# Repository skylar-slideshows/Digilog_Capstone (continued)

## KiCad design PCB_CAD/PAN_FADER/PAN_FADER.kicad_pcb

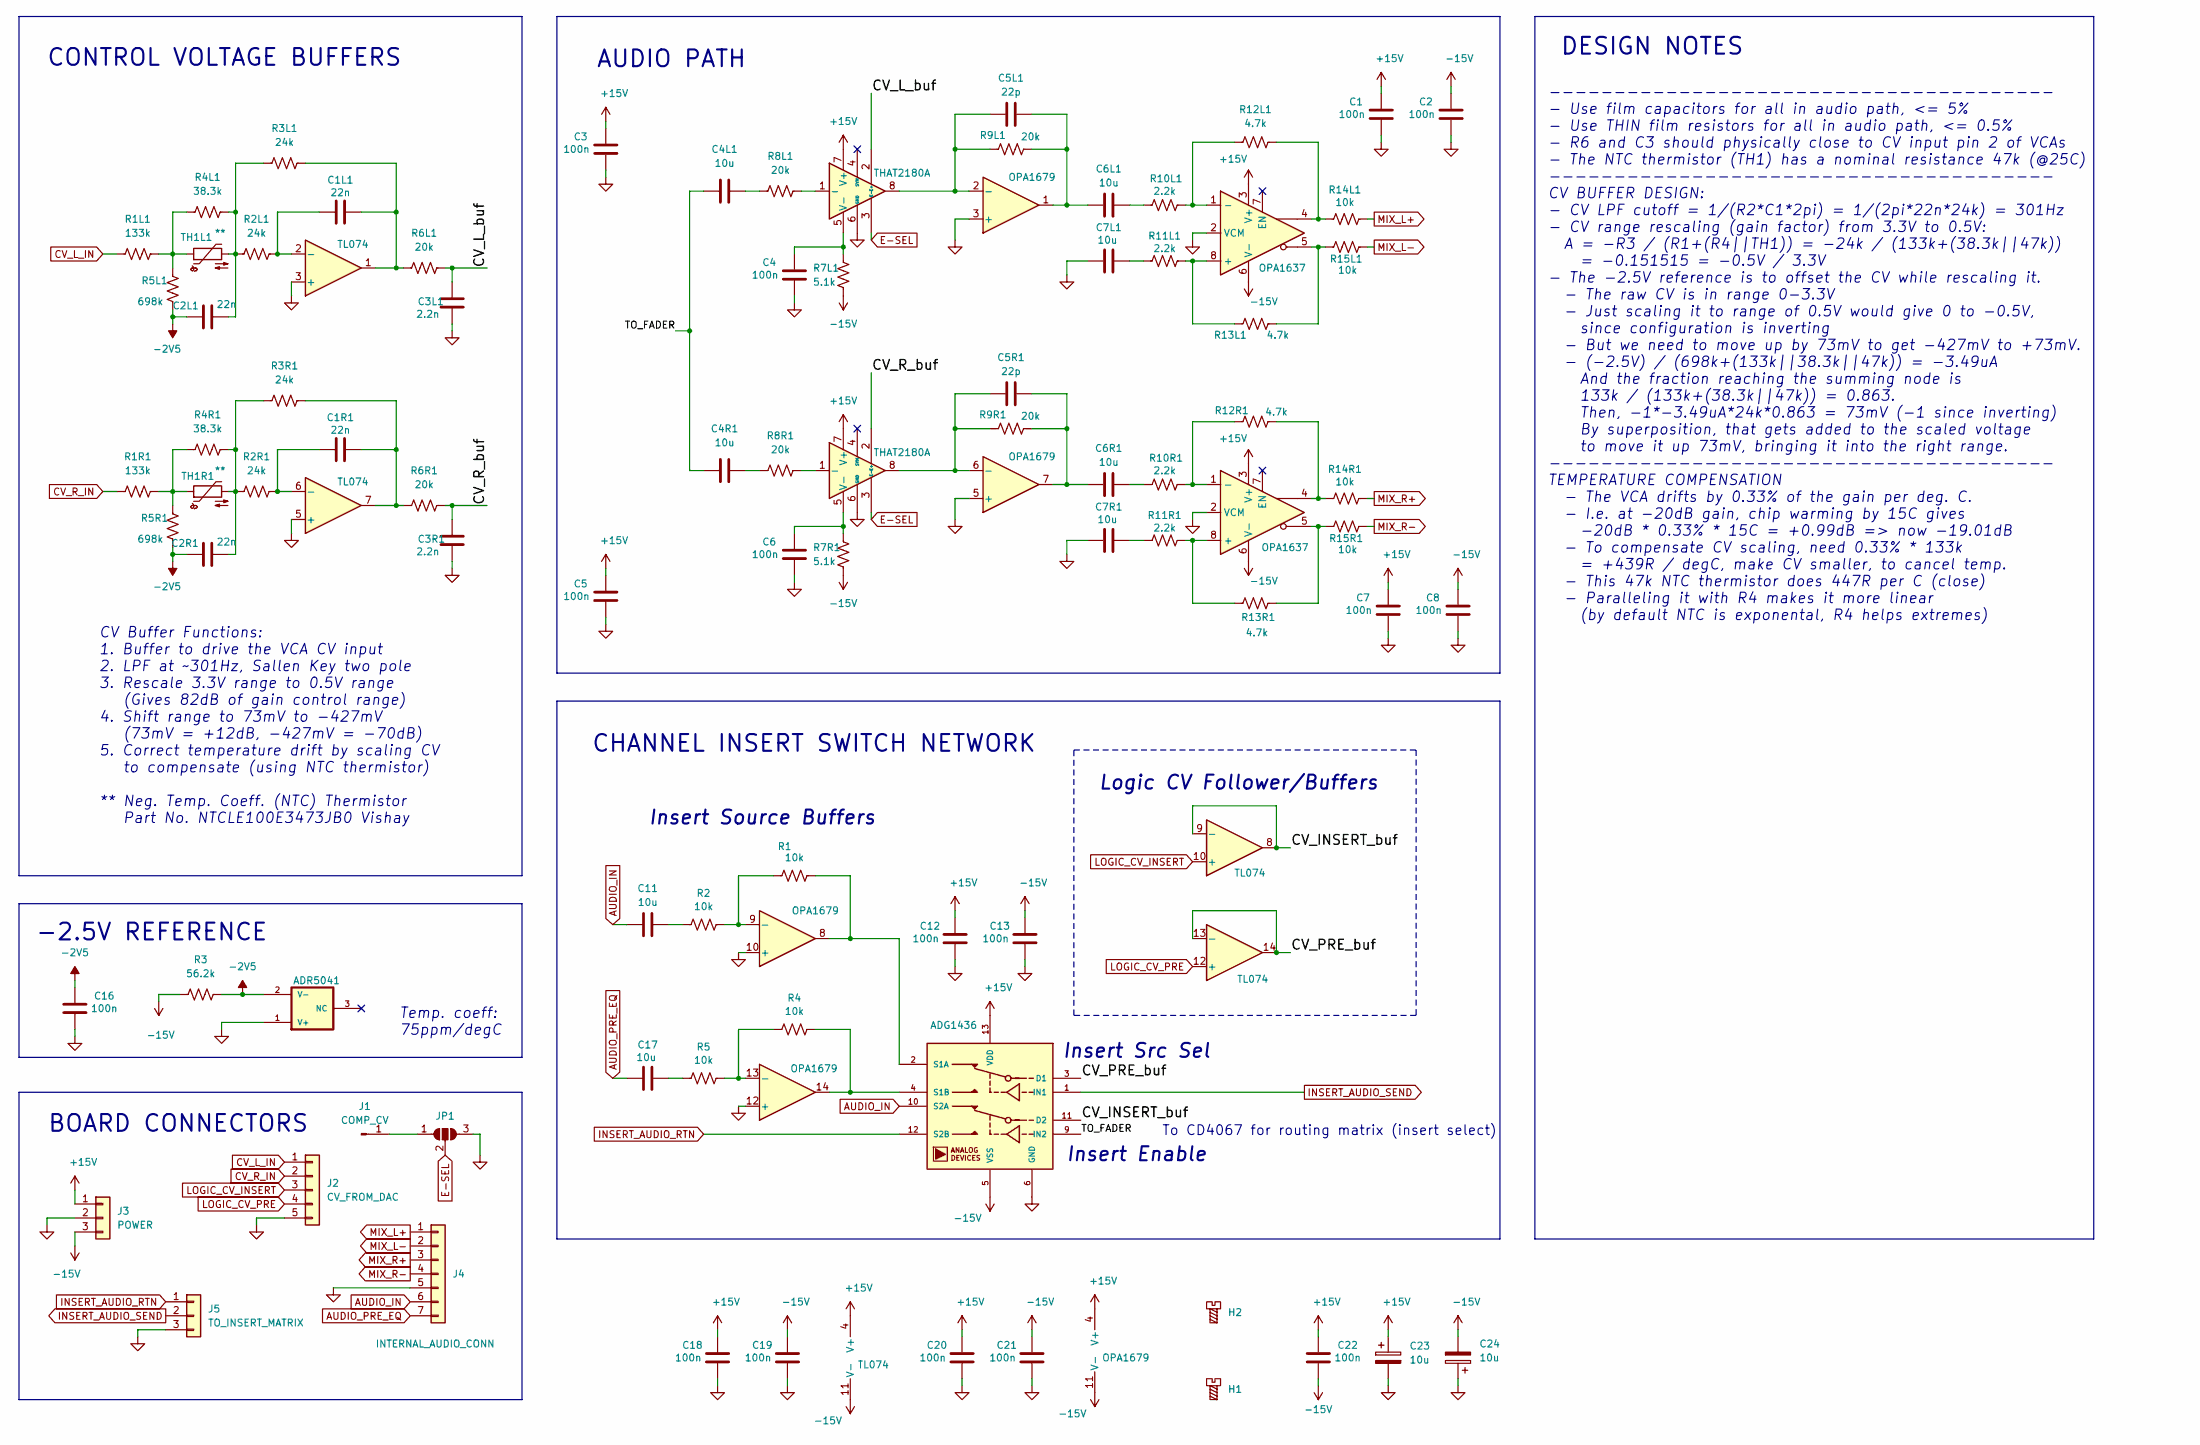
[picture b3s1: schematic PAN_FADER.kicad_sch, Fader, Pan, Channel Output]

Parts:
C1, C2, C3, C4, C5, C6, C7, C8, C12, C13, C16, C18, C19, C20, C21, C22: 100n; C_0603_1608Metric; LCSC C1591
C1L1, C1R1, C2L1, C2R1: 22n; C_Rect_L7.2mm_W2.5mm_P5.00mm; LCSC DNP
C3L1, C3R1: 2.2n; C_Rect_L7.2mm_W2.5mm_P5.00mm; LCSC DNP
C4L1, C4R1, C6L1, C6R1, C7L1, C7R1, C11, C17: 10u; CP_Elec_6.3x5.4_Nichicon; LCSC C340735
C5L1, C5R1: 22p; C_0603_1608Metric; LCSC C105620
C23, C24: 10u; C_1206_3216Metric; LCSC C9807
H1, H2: MountingHole_Pad; MountingHole_2.2mm_M2
J1: COMP_CV; PinHeader_1x01_P2.54mm_Vertical; LCSC DNP
J2: CV_FROM_DAC; PinHeader_1x05_P2.54mm_Vertical; Part Number 1-0301FBV0T; LCSC DNP
J3: POWER; PinHeader_1x03_P2.54mm_Vertical; Part Number 1-0301FBV0T; LCSC DNP
J4: INTERNAL_AUDIO_CONN; PinHeader_1x07_P2.54mm_Vertical; Part Number 1-0301FBV0T; LCSC DNP
J5: TO_INSERT_MATRIX; PinHeader_1x03_P2.54mm_Vertical; Part Number 1-0301FBV0T; LCSC DNP
JP1: SolderJumper_3_Open; SolderJumper-3_P2.0mm_Open_TrianglePad1.0x1.5mm; LCSC DNP
R1, R2, R4, R5, R14L1, R14R1, R15L1, R15R1: 10k; R_0603_1608Metric; LCSC C95204
R1L1, R1R1: 133k; R_0402_1005Metric; LCSC C852517
R2L1, R2R1, R3L1, R3R1: 24k; R_0603_1608Metric; LCSC C319717
R3: 56.2k; R_0402_1005Metric; LCSC C705626
R4L1, R4R1: 38.3k; R_0603_1608Metric; LCSC C861362
R5L1, R5R1: 698k; R_0805_2012Metric; LCSC C865618
R6L1, R6R1, R8L1, R8R1, R9L1, R9R1: 20k; R_0603_1608Metric; LCSC C154077
R7L1, R7R1: 5.1k; R_0603_1608Metric; LCSC C122969
R10L1, R10R1, R11L1, R11R1: 2.2k; R_0402_1005Metric; LCSC C326602
R12L1, R12R1, R13L1, R13R1: 4.7k; R_0402_1005Metric; LCSC C281778
TH1L1, TH1R1: **; R_Axial_DIN0207_L6.3mm_D2.5mm_P2.54mm_Vertical; LCSC DNP
U1, U5: THAT2180A; SIP-8_19x3mm_P2.54mm; LCSC DNP
U2: OPA1679; SOIC-14_3.9x8.65mm_Pitch1.27mm; LCSC C2878631
U3, U7: OPA1637; Texas_S-PDSO-G8_3x3mm_P0.65mm; LCSC C2860968
U4: TL074; SOIC-14_3.9x8.7mm_P1.27mm; LCSC C12594
U8: ADR5041; SOT-23-3; MPN ADR5041ARTZ-R2; LCSC C659596
U9: ADG1436; TSSOP-16_4.4x5mm_P0.65mm; LCSC C408899

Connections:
+15V: C1.2, C3.2, C5.2, C7.2, C12.2, C18.2, C20.2, C22.2, C23.1, J3.1, U1.7 (V+), U2.4 (V+), U3.3 (V+), U4.4 (V+), U5.7 (V+), U7.3 (V+), U9.13 (VDD)
-2V5: C2L1.1, C2R1.1, C16.2, R3.2, R5L1.1, R5R1.1, U8.2 (V-)
-15V: C2.2, C8.2, C13.2, C19.2, C21.2, C22.1, C24.2, J3.3, R3.1, R7L1.1, R7R1.1, U2.11 (V-), U3.6 (V-), U4.11 (V-), U7.6 (V-), U9.5 (VSS)
/CV_INSERT_buf: U4.8, U4.9 (-), U9.11 (D2)
/CV_L_buf: C3L1.2, R6L1.2, U1.2 (E+)
/CV_PRE_buf: U4.13 (-), U4.14, U9.3 (D1)
/CV_R_buf: C3R1.2, R6R1.2, U5.2 (E+)
/TO_FADER: C4L1.1, C4R1.1, U9.9 (IN2)
AUDIO_IN: C11.1, J4.6, U9.10 (S2A)
AUDIO_PRE_EQ: C17.1, J4.7
CV_L_IN: J2.1, R1L1.1
CV_R_IN: J2.2, R1R1.1
E-SEL: JP1.2 (C), U1.3 (E-), U5.3 (E-)
GND: C1.1, C2.1, C3.1, C3L1.1, C3R1.1, C4.1, C5.1, C6.1, C7.1, C7L1.1, C7R1.1, C8.1, C12.1, C13.1, C16.1, C18.1, C19.1, C20.1, C21.1, C23.2, C24.1, J2.5, J3.2, J4.5, J5.3, JP1.3 (B), U1.6 (GND), U2.3 (+), U2.5 (+), U2.10 (+), U2.12 (+), U3.2 (VCM), U4.3 (+), U4.5 (+), U5.6 (GND), U7.2 (VCM), U8.1 (V+), U9.6 (GND)
INSERT_AUDIO_RTN: J5.1, U9.12 (S2B)
INSERT_AUDIO_SEND: J5.2, U9.1 (IN1)
LOGIC_CV_INSERT: J2.3, U4.10 (+)
LOGIC_CV_PRE: J2.4, U4.12 (+)
MIX_L+: J4.1, R14L1.2
MIX_L-: J4.2, R15L1.2
MIX_R+: J4.3, R14R1.2
MIX_R-: J4.4, R15R1.2
unnamed: C1L1.2, R3L1.2, R6L1.1, U4.1
unnamed: C1R1.2, R3R1.2, R6R1.1, U4.7
unnamed: C2L1.2, R2L1.1, R3L1.1, R4L1.2, TH1L1.2
unnamed: C2R1.2, R2R1.1, R3R1.1, R4R1.2, TH1R1.2
unnamed: C4L1.2, R8L1.1
unnamed: C4R1.2, R8R1.1
unnamed: C5L1.2, C6L1.1, R9L1.2, U2.1
unnamed: C5R1.2, C6R1.1, R9R1.2, U2.7
unnamed: C6L1.2, R10L1.1
unnamed: C6R1.2, R10R1.1
unnamed: C7L1.2, R11L1.1
unnamed: C7R1.2, R11R1.1
unnamed: C11.2, R2.2
unnamed: C17.2, R5.2
unnamed: J1.1 (Pin_1_1), JP1.1 (A)
unnamed: R1L1.2, R4L1.1, R5L1.2, TH1L1.1
unnamed: R1R1.2, R4R1.1, R5R1.2, TH1R1.1
unnamed: R12L1.2, R14L1.1, U3.4
unnamed: R12R1.2, R14R1.1, U7.4
unnamed: R13L1.2, R15L1.1, U3.5
unnamed: R13R1.2, R15R1.1, U7.5
unnamed: R8L1.2, U1.1 (-)
unnamed: C4.2, R7L1.2, U1.5 (V-)
unnamed: C5L1.1, R9L1.1, U1.8, U2.2 (-)
unnamed: C5R1.1, R9R1.1, U2.6 (-), U5.8
unnamed: R1.2, R2.1, U2.9 (-)
unnamed: R4.2, R5.1, U2.13 (-)
unnamed: R11L1.2, R13L1.1, U3.8 (+)
unnamed: R10L1.2, R12L1.1, U3.1 (-)
unnamed: C1L1.1, R2L1.2, U4.2 (-)
unnamed: C1R1.1, R2R1.2, U4.6 (-)
unnamed: R8R1.2, U5.1 (-)
unnamed: C6.2, R7R1.2, U5.5 (V-)
unnamed: R11R1.2, R13R1.1, U7.8 (+)
unnamed: R10R1.2, R12R1.1, U7.1 (-)
unnamed: R1.1, U2.8, U9.2 (S1A)
unnamed: R4.1, U2.14, U9.4 (S1B)

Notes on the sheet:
CONTROL VOLTAGE BUFFERS
--------------------------------------- - Use film capacitors for all in audio path, <= 5% - Use THIN film resistors for all in audio path, <= 0.5% - R6 and C3 should physically close to CV input pin 2 of VCAs - The NTC thermistor (TH1) has a nominal resistance 47k (@25C) --------------------------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
BOARD CONNECTORS
Logic CV Follower/Buffers
CV Buffer Functions: 1. Buffer to drive the VCA CV input 2. LPF at ~301Hz, Sallen Key two pole 3. Rescale 3.3V range to 0.5V range (Gives 82dB of gain control range) 4. Shift range to 73mV to -427mV (73mV = +12dB, -427mV = -70dB) 5. Correct temperature drift by scaling CV to compensate (using NTC t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
Insert Source Buffers
Insert Enable
AUDIO PATH
Insert Src Sel
-2.5V REFERENCE
CHANNEL INSERT SWITCH NETWORK
Temp. coeff: 75ppm/degC
DESIGN NOTES
To CD4067 for routing matrix (insert select)

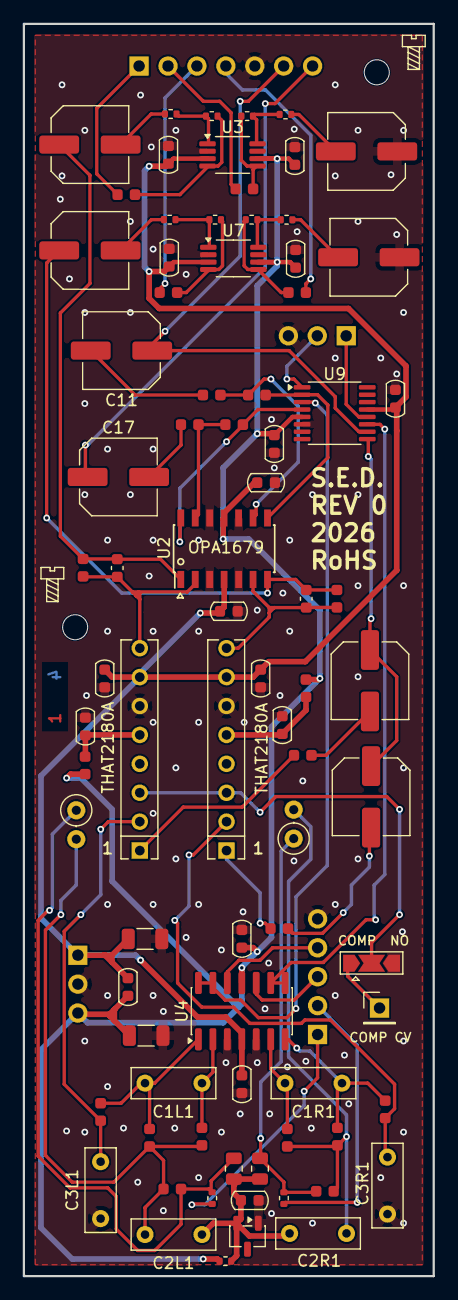
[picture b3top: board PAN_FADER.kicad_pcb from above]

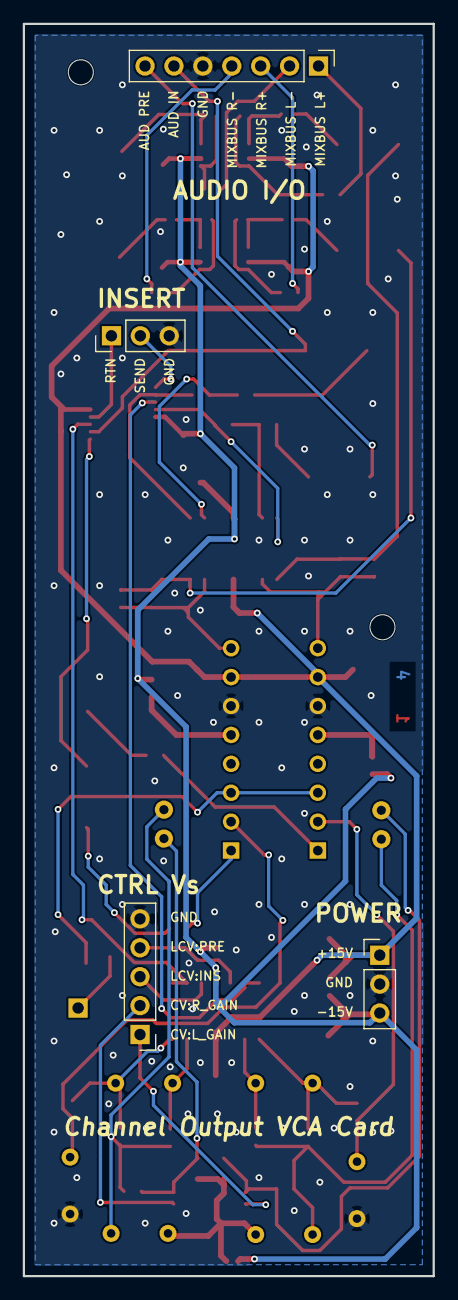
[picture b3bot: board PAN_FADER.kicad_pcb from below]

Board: 4 copper layers, 36.0 x 110.0 mm, 87 parts (4 on the bottom side), 59 nets.

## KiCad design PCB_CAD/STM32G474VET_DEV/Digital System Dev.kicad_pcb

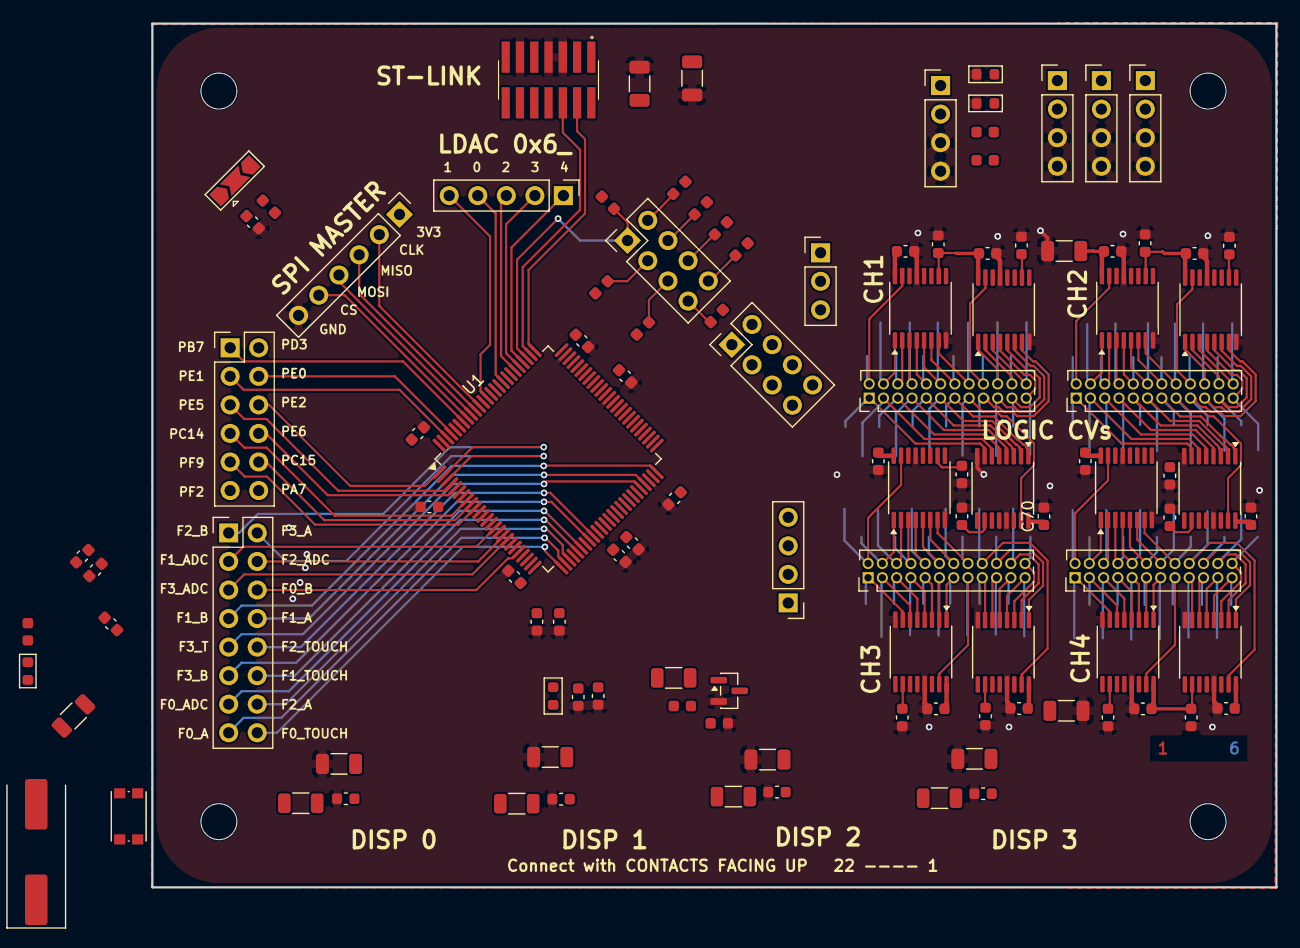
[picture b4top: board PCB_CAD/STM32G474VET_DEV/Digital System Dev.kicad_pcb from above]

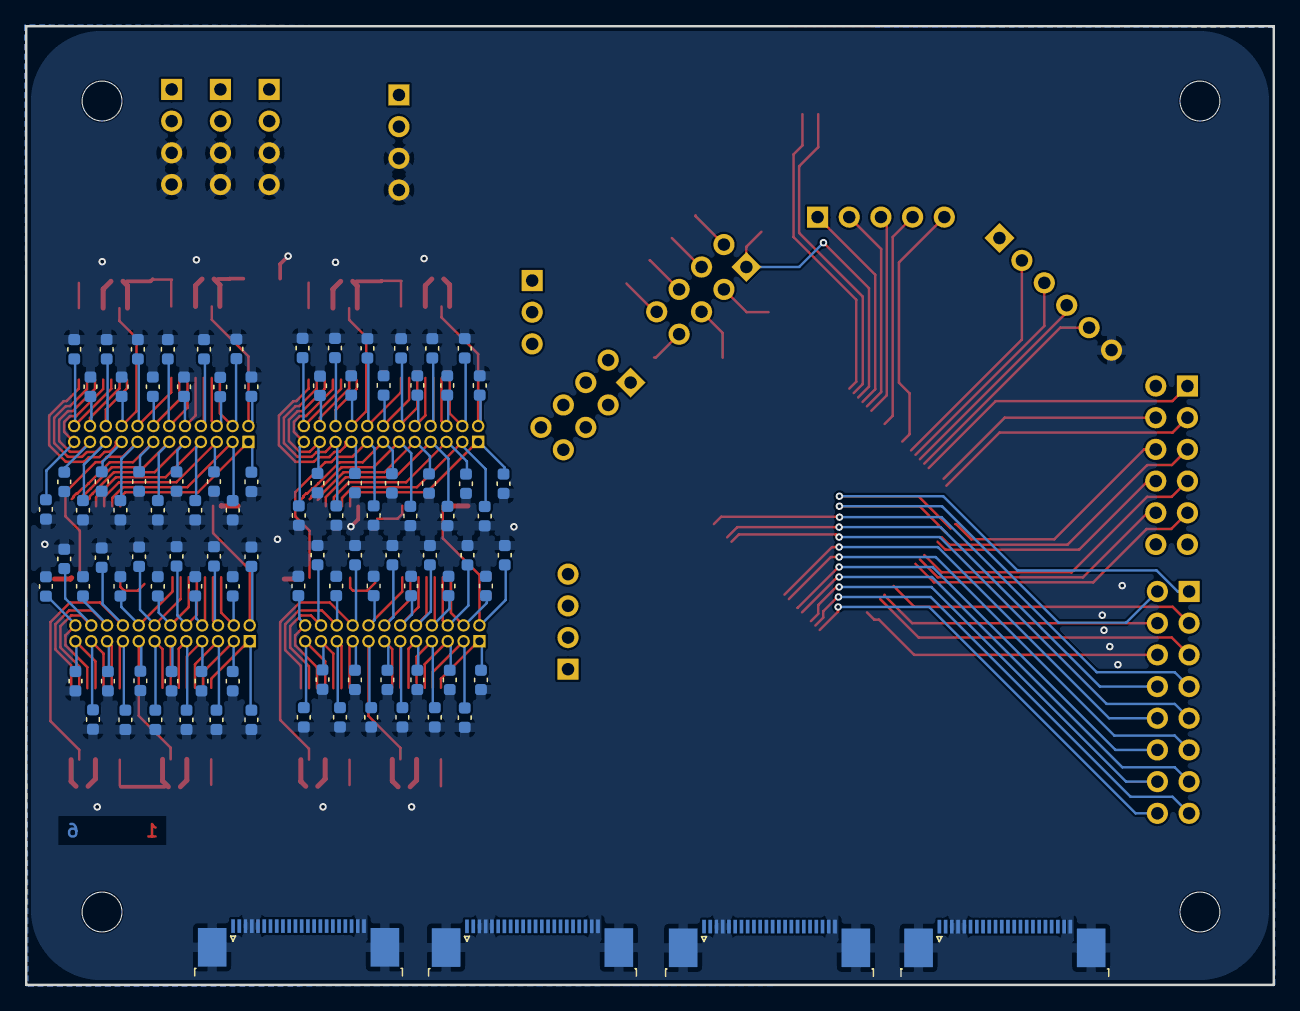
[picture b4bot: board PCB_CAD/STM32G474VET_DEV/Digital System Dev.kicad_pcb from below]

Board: 6 copper layers, 100.0 x 76.8 mm, 214 parts (100 on the bottom side), 209 nets.

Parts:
C1, C2: 20p; C_0603_1608Metric
C3, C5, C7, C8, C9, C10, C11, C12, C13, C14, C15, C16, C35, C36, C37, C38, C62, C63, C64, C65, C66, C67, C68, C69, C70, C71, C72, C73, C74, C75, C76, C77, C78, C79, C80, C81, C82, C83, C84, C85, C86, C87, C88, C89, C90, C91, C92, C93, C94, C95, C96, C97, C98, C99, C100, C101, C102, C103, C104, C105, C106, C107, C108, C109, C110, C111, C112, C113, C114, C115, C116, C117, C118, C119, C120, C121, C122, C123, C124, C125, C126, C127, C128, C129, C130, C131, C132, C133, C134, C135, C136, C137, C138, C139, C140, C141, C142, C143, C144, C145, C146, C147, C148, C149, C150, C151, C152, C153, C154, C155, C156, C157, C158, C159, C160, C161, C162, C163, C164, C165, C166, C167, C168, C169, C170, C171, C172, C173, C174, C175, C176, C177, C178, C179, C180, C181: 100n; C_0603_1608Metric
C4, C6: 1u; C_0603_1608Metric
C41, C42, C47, C48, C49, C50, C60, C61: 10u; C_1206_3216Metric
D3, D6, D7: LED; LED_0603_1608Metric
FB1: FerriteBead; Ferrite_0603_1608Metric
H1, H2, H3, H4: MountingScrew; MountingHole_3.2mm_M3
J1: STLINK; FTSH-107-01-L-DV-K-TR
J7: SPI_MASTER; PinHeader_1x06_P2.54mm_Vertical
J9, J12, J13, J14: EXT_POW_IN; PinHeader_1x04_P2.54mm_Vertical
J15: LDAC; PinHeader_1x05_P2.54mm_Vertical
J16: FADER; PinHeader_2x08_P2.54mm_Vertical
J17: DISP0; TE_2-1734839-2_1x22-1MP_P0.5mm_Horizontal
J18: DISP1; TE_2-1734839-2_1x22-1MP_P0.5mm_Horizontal
J19: DISP2; TE_2-1734839-2_1x22-1MP_P0.5mm_Horizontal
J20: DISP3; TE_2-1734839-2_1x22-1MP_P0.5mm_Horizontal
J21: EXTRA; PinHeader_2x06_P2.54mm_Vertical
J22: COMP; PinHeader_2x04_P2.54mm_Vertical
J23: LEDs; PinHeader_1x04_P2.54mm_Vertical
J24: I2C; PinHeader_2x04_P2.54mm_Vertical
J25: SHIFTREG; PinHeader_1x03_P2.54mm_Vertical
J26: CV_SW_1; PinHeader_2x12_P1.27mm_Vertical
J27: CV_SW_2; PinHeader_2x12_P1.27mm_Vertical
J28: CV_SW_4; PinHeader_2x12_P1.27mm_Vertical
J29: CV_SW_3; PinHeader_2x12_P1.27mm_Vertical
Q1: 2N7002; SOT-23
R1, R18, R19, R20, R21: 390; R_1206_3216Metric
R2: 10k; R_0603_1608Metric
R7, R8, R9, R10, R11, R12, R13, R14: 1.5k; R_0603_1608Metric
R23, R24: 680; R_0603_1608Metric
R25: 68; R_1206_3216Metric
R26, R27: 47k; R_0603_1608Metric
R28: 3.3k; R_0603_1608Metric
SP1: BOOT_MODE; SolderJumper-3_P2.0mm_Open_TrianglePad1.0x1.5mm
SW1: RESET; SW_Push_1P1T_NO_CK_KMR2
U1: STM32G474VETx; LQFP-100_14x14mm_P0.5mm
U28, U29, U30, U31, U32, U33, U34, U35, U36, U37, U38, U39: 74HC595; TSSOP-16_4.4x5mm_P0.65mm
X1: HSE_24; Crystal_SMD_HC49-SD

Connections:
+3.3VA: C4.1, C5.1, C6.1, C7.1, FB1.2, U1.36 (VREF+), U1.37 (VDDA)
+3V3: C8.1, C9.1, C10.1, C11.1, C12.1, C13.1, C14.1, C15.1, C35.1, C36.1, C37.1, C38.1, C41.1, C42.1, C47.1, C48.1, C49.1, C50.1, C60.1, C61.1, C62.1, C63.1, C64.1, C65.1, C66.1, C67.1, C68.1, C69.1, C70.1, C71.1, C72.1, C73.1, C170.1, C171.1, C172.1, C173.1, C174.1, C175.1, C176.1, C177.1, C178.1, C179.1, C180.1, C181.1, FB1.1, J1.3 (VCC), J7.1, J9.1, J12.1, J13.1, J14.1, J17.6, J18.6, J19.6, J20.6, R7.1, R8.1, R9.1, R10.1, R11.1, R12.1, R13.1, R14.1, R24.1, SP1.3 (B), U1.6 (VBAT), U1.24 (VDD), U1.49 (VDD), U1.64 (VDD), U1.75 (VDD), U1.100 (VDD), U28.10 (~SRCLR), U28.16 (VCC), U29.10 (~SRCLR), U29.16 (VCC), U30.10 (~SRCLR), U30.16 (VCC), U31.10 (~SRCLR), U31.16 (VCC), U32.10 (~SRCLR), U32.16 (VCC), U33.10 (~SRCLR), U33.16 (VCC), U34.10 (~SRCLR), U34.16 (VCC), U35.10 (~SRCLR), U35.16 (VCC), U36.10 (~SRCLR), U36.16 (VCC), U37.10 (~SRCLR), U37.16 (VCC), U38.10 (~SRCLR), U38.16 (VCC), U39.10 (~SRCLR), U39.16 (VCC)
+5V: J9.2, J12.2, J13.2, J14.2, R18.2, R19.2, R20.2, R21.2, R28.1
/cv_sw/1_1: C121.1, J26.23, U32.4 (QE)
/cv_sw/1_2: C122.1, J26.2, U28.15 (QA)
/cv_sw/1_3: C120.1, J26.21, U32.5 (QF)
/cv_sw/1_4: C123.1, J26.4, U28.1 (QB)
/cv_sw/1_5: C119.1, J26.19, U32.6 (QG)
/cv_sw/1_6: C124.1, J26.6, U28.2 (QC)
/cv_sw/1_7: C118.1, J26.17, U32.7 (QH)
/cv_sw/1_8: C125.1, J26.8, U28.3 (QD)
/cv_sw/1_9: C117.1, J26.15, U36.15 (QA)
/cv_sw/1_10: C126.1, J26.10, U28.4 (QE)
/cv_sw/1_11: C116.1, J26.13, U36.1 (QB)
/cv_sw/1_12: C127.1, J26.12, U28.5 (QF)
/cv_sw/1_13: C133.1, J26.11, U36.2 (QC)
/cv_sw/1_14: C110.1, J26.14, U28.6 (QG)
/cv_sw/1_15: C132.1, J26.9, U36.3 (QD)
/cv_sw/1_16: C111.1, J26.16, U28.7 (QH)
/cv_sw/1_17: C131.1, J26.7, U36.4 (QE)
/cv_sw/1_18: C112.1, J26.18, U32.15 (QA)
/cv_sw/1_19: C130.1, J26.5, U36.5 (QF)
/cv_sw/1_20: C113.1, J26.20, U32.1 (QB)
/cv_sw/1_21: C129.1, J26.3, U36.6 (QG)
/cv_sw/1_22: C114.1, J26.22, U32.2 (QC)
/cv_sw/1_23: C128.1, J26.1, U36.7 (QH)
/cv_sw/1_24: C115.1, J26.24, U32.3 (QD)
/cv_sw/2_1: C97.1, J27.23, U33.4 (QE)
/cv_sw/2_2: C146.1, J27.2, U29.15 (QA)
/cv_sw/2_3: C96.1, J27.21, U33.5 (QF)
/cv_sw/2_4: C147.1, J27.4, U29.1 (QB)
/cv_sw/2_5: C95.1, J27.19, U33.6 (QG)
/cv_sw/2_6: C148.1, J27.6, U29.2 (QC)
/cv_sw/2_7: C94.1, J27.17, U33.7 (QH)
/cv_sw/2_8: C149.1, J27.8, U29.3 (QD)
/cv_sw/2_9: C93.1, J27.15, U37.15 (QA)
/cv_sw/2_10: C150.1, J27.10, U29.4 (QE)
/cv_sw/2_11: C92.1, J27.13, U37.1 (QB)
/cv_sw/2_12: C151.1, J27.12, U29.5 (QF)
/cv_sw/2_13: C157.1, J27.11, U37.2 (QC)
/cv_sw/2_14: C86.1, J27.14, U29.6 (QG)
/cv_sw/2_15: C156.1, J27.9, U37.3 (QD)
/cv_sw/2_16: C87.1, J27.16, U29.7 (QH)
/cv_sw/2_17: C155.1, J27.7, U37.4 (QE)
/cv_sw/2_18: C88.1, J27.18, U33.15 (QA)
/cv_sw/2_19: C154.1, J27.5, U37.5 (QF)
/cv_sw/2_20: C89.1, J27.20, U33.1 (QB)
/cv_sw/2_21: C153.1, J27.3, U37.6 (QG)
/cv_sw/2_22: C90.1, J27.22, U33.2 (QC)
/cv_sw/2_23: C152.1, J27.1, U37.7 (QH)
/cv_sw/2_24: C91.1, J27.24, U33.3 (QD)
/cv_sw/3_1: C109.1, J29.23, U34.4 (QE)
/cv_sw/3_2: C134.1, J29.2, U30.15 (QA)
/cv_sw/3_3: C108.1, J29.21, U34.5 (QF)
/cv_sw/3_4: C135.1, J29.4, U30.1 (QB)
/cv_sw/3_5: C107.1, J29.19, U34.6 (QG)
/cv_sw/3_6: C136.1, J29.6, U30.2 (QC)
/cv_sw/3_7: C106.1, J29.17, U34.7 (QH)
/cv_sw/3_8: C137.1, J29.8, U30.3 (QD)
/cv_sw/3_9: C105.1, J29.15, U38.15 (QA)
/cv_sw/3_10: C138.1, J29.10, U30.4 (QE)
/cv_sw/3_11: C104.1, J29.13, U38.1 (QB)
/cv_sw/3_12: C139.1, J29.12, U30.5 (QF)
/cv_sw/3_13: C145.1, J29.11, U38.2 (QC)
/cv_sw/3_14: C98.1, J29.14, U30.6 (QG)
/cv_sw/3_15: C144.1, J29.9, U38.3 (QD)
/cv_sw/3_16: C99.1, J29.16, U30.7 (QH)
/cv_sw/3_17: C143.1, J29.7, U38.4 (QE)
/cv_sw/3_18: C100.1, J29.18, U34.15 (QA)
/cv_sw/3_19: C142.1, J29.5, U38.5 (QF)
/cv_sw/3_20: C101.1, J29.20, U34.1 (QB)
/cv_sw/3_21: C141.1, J29.3, U38.6 (QG)
/cv_sw/3_22: C102.1, J29.22, U34.2 (QC)
/cv_sw/3_23: C140.1, J29.1, U38.7 (QH)
/cv_sw/3_24: C103.1, J29.24, U34.3 (QD)
/cv_sw/4_1: C79.1, J28.23, U35.4 (QE)
/cv_sw/4_2: C164.1, J28.2, U31.15 (QA)
/cv_sw/4_3: C78.1, J28.21, U35.5 (QF)
/cv_sw/4_4: C165.1, J28.4, U31.1 (QB)
/cv_sw/4_5: C77.1, J28.19, U35.6 (QG)
/cv_sw/4_6: C166.1, J28.6, U31.2 (QC)
/cv_sw/4_7: C76.1, J28.17, U35.7 (QH)
/cv_sw/4_8: C167.1, J28.8, U31.3 (QD)
/cv_sw/4_9: C75.1, J28.15, U39.15 (QA)
/cv_sw/4_10: C168.1, J28.10, U31.4 (QE)
/cv_sw/4_11: C74.1, J28.13, U39.1 (QB)
/cv_sw/4_12: C169.1, J28.12, U31.5 (QF)
/cv_sw/4_13: C163.1, J28.11, U39.2 (QC)
/cv_sw/4_14: C85.1, J28.14, U31.6 (QG)
/cv_sw/4_15: C162.1, J28.9, U39.3 (QD)
/cv_sw/4_16: C84.1, J28.16, U31.7 (QH)
/cv_sw/4_17: C161.1, J28.7, U39.4 (QE)
/cv_sw/4_18: C83.1, J28.18, U35.15 (QA)
/cv_sw/4_19: C160.1, J28.5, U39.5 (QF)
/cv_sw/4_20: C82.1, J28.20, U35.1 (QB)
/cv_sw/4_21: C159.1, J28.3, U39.6 (QG)
/cv_sw/4_22: C81.1, J28.22, U35.2 (QC)
/cv_sw/4_23: C158.1, J28.1, U39.7 (QH)
/cv_sw/4_24: C80.1, J28.24, U35.3 (QD)
COMP_ADC0: J22.7, U1.51 (PB12)
COMP_ADC1: J22.4, U1.57 (PD10)
COMP_ADC2: J22.1, U1.60 (PD13)
COMP_ADC3: J22.6, U1.55 (PD8)
COMP_CV0: J22.5, U1.56 (PD9)
COMP_CV1: J22.8, U1.32 (PB0)
COMP_CV2: J22.3, U1.58 (PD11)
COMP_CV3: J22.2, U1.59 (PD12)
DAC_LDAC0: J15.4, U1.84 (PD2)
DAC_LDAC1: J15.5, U1.88 (PD6)
DAC_LDAC2: J15.3, U1.81 (PC12)
DAC_LDAC3: J15.2, U1.80 (PC11)
DAC_LDAC4: J15.1, U1.79 (PC10)
DISP_A0_FMC: J17.17, J18.17, J19.17, J20.17, U1.11 (PF10)
DISP_BL-: J17.2, J18.2, J19.2, J20.2, Q1.3 (D)
DISP_CS0: J17.18, U1.45 (PE14)
DISP_CS1: J18.18, U1.44 (PE13)
DISP_CS2: J19.18, U1.43 (PE12)
DISP_CS3: J20.18, U1.42 (PE11)
DISP_D0_FMC: J17.14, J18.14, J19.14, J20.14, U1.61 (PD14)
DISP_D1_FMC: J17.13, J18.13, J19.13, J20.13, U1.62 (PD15)
DISP_D2_FMC: J17.12, J18.12, J19.12, J20.12, U1.82 (PD0)
DISP_D3_FMC: J17.11, J18.11, J19.11, J20.11, U1.83 (PD1)
DISP_D4_FMC: J17.10, J18.10, J19.10, J20.10, U1.38 (PE7)
DISP_D5_FMC: J17.9, J18.9, J19.9, J20.9, U1.39 (PE8)
DISP_D6_FMC: J17.8, J18.8, J19.8, J20.8, U1.40 (PE9)
DISP_D7_FMC: J17.7, J18.7, J19.7, J20.7, U1.41 (PE10)
DISP_NOE_FMC: J17.15, J18.15, J19.15, J20.15, U1.86 (PD4)
DISP_NWE_FMC: J17.16, J18.16, J19.16, J20.16, U1.87 (PD5)
DISP_PWM: R25.1, U1.71 (PA10)
DISP_RST: J17.20, J18.20, J19.20, J20.20, U1.7 (PC13)
F0_ADC: J16.13, U1.30 (PC4)
F0_MoA: J16.15, U1.27 (PA5)
F0_MoB: J16.6, U1.21 (PA1)
F0_Touch: J16.16, U1.26 (PA4)
F1_ADC: J16.3, U1.15 (PC0)
F1_MoA: J16.8, U1.47 (PB10)
F1_MoB: J16.7, U1.50 (PB11)
F1_Touch: J16.12, U1.31 (PC5)
F2_ADC: J16.4, U1.17 (PC2)
F2_MoA: J16.14, U1.28 (PA6)
F2_MoB: J16.1, U1.2 (PE3)
F2_Touch: J16.10, U1.34 (PB2)
F3_ADC: J16.5, U1.18 (PC3)
F3_MoA: J16.2, U1.3 (PE4)
F3_MoB: J16.11, U1.33 (PB1)
F3_Touch: J16.9, U1.46 (PE15)
GND: C1.2, C2.1, C3.1, C4.2, C5.2, C6.2, C7.2, C8.2, C9.2, C10.2, C11.2, C12.2, C13.2, C14.2, C15.2, C16.2, C35.2, C36.2, C37.2, C38.2, C41.2, C42.2, C47.2, C48.2, C49.2, C50.2, C60.2, C61.2, C62.2, C63.2, C64.2, C65.2, C66.2, C67.2, C68.2, C69.2, C70.2, C71.2, C72.2, C73.2, C74.2, C75.2, C76.2, C77.2, C78.2, C79.2, C80.2, C81.2, C82.2, C83.2, C84.2, C85.2, C86.2, C87.2, C88.2, C89.2, C90.2, C91.2, C92.2, C93.2, C94.2, C95.2, C96.2, C97.2, C98.2, C99.2, C100.2, C101.2, C102.2, C103.2, C104.2, C105.2, C106.2, C107.2, C108.2, C109.2, C110.2, C111.2, C112.2, C113.2, C114.2, C115.2, C116.2, C117.2, C118.2, C119.2, C120.2, C121.2, C122.2, C123.2, C124.2, C125.2, C126.2, C127.2, C128.2, C129.2, C130.2, C131.2, C132.2, C133.2, C134.2, C135.2, C136.2, C137.2, C138.2, C139.2, C140.2, C141.2, C142.2, C143.2, C144.2, C145.2, C146.2, C147.2, C148.2, C149.2, C150.2, C151.2, C152.2, C153.2, C154.2, C155.2, C156.2, C157.2, C158.2, C159.2, C160.2, C161.2, C162.2, C163.2, C164.2, C165.2, C166.2, C167.2, C168.2, C169.2, C170.2, C171.2, C172.2, C173.2, C174.2, C175.2, C176.2, C177.2, C178.2, C179.2, C180.2, C181.2, D3.1 (K), D6.1 (K), D7.1 (K), J1.5 (GND), J1.7 (GND), J1.11 (GNDDetect), J7.6, J9.3, J9.4, J12.3, J12.4, J13.3, J13.4, J14.3, J14.4, J17.3, J17.4, J17.5, J17.21, J17.22, J17.MP (MountPin), J18.3, J18.4, J18.5, J18.21, J18.22, J18.MP (MountPin), J19.3, J19.4, J19.5, J19.21, J19.22, J19.MP (MountPin), J20.3, J20.4, J20.5, J20.21, J20.22, J20.MP (MountPin), Q1.2 (S), R27.2, SW1.1, U1.23 (VSS), U1.35 (VSSA), U1.48 (VSS), U1.63 (VSS), U1.74 (VSS), U1.99 (VSS), U28.8 (GND), U28.13 (~OE), U29.8 (GND), U29.13 (~OE), U30.8 (GND), U30.13 (~OE), U31.8 (GND), U31.13 (~OE), U32.8 (GND), U32.13 (~OE), U33.8 (GND), U33.13 (~OE), U34.8 (GND), U34.13 (~OE), U35.8 (GND), U35.13 (~OE), U36.8 (GND), U36.13 (~OE), U37.8 (GND), U37.13 (~OE), U38.8 (GND), U38.13 (~OE), U39.8 (GND), U39.13 (~OE)
I2C1_Clock: J24.1, R7.2, U1.78 (PA15)
I2C1_Data: J24.2, R8.2, U1.96 (PB9)
I2C2_Clock: J24.3, R9.2, U1.70 (PA9)
I2C2_Data: J24.4, R10.2, U1.69 (PA8)
I2C3_Clock: J24.6, R11.2, U1.67 (PC8)
I2C3_Data: J24.5, R12.2, U1.68 (PC9)
I2C4_Clock: J24.8, R13.2, U1.65 (PC6)
I2C4_Data: J24.7, R14.2, U1.66 (PC7)
LED_Clock: J23.3, U1.54 (PB15)
LED_Data: J23.1, U1.52 (PB13)
LED_Latch: J23.2, U1.53 (PB14)
LED_PWM: J23.4, U1.16 (PC1)
LED_TEST: J21.11, R23.1, U1.19 (PF2)
MASTER_CS_IN: J7.5, U1.93 (PB6)
MASTER_Clock: J7.2, U1.90 (PB3)
MASTER_MISO: J7.3, U1.91 (PB4)
MASTER_MOSI: J7.4, U1.92 (PB5)
NRST: C3.2, J1.12 (~RST), SW1.2, U1.14 (PG10)
unnamed: C2.2, R1.1, X1.2
unnamed: D3.2 (A), R23.2
unnamed: D6.2 (A), R24.2
unnamed: D7.2 (A), R28.2
unnamed: J17.1, R18.1
unnamed: J18.1, R19.1
unnamed: J19.1, R20.1
unnamed: J20.1, R21.1
unnamed: Q1.1 (G), R25.2, R26.1
unnamed: R26.2, R27.1
unnamed: C16.1, SP1.1 (A)
unnamed: R2.2, SP1.2 (C)
unnamed: R2.1, U1.95 (PB8)
unnamed: C1.1, U1.12 (PF0), X1.1
unnamed: R1.2, U1.13 (PF1)
unnamed: U28.9 (QH'), U32.14 (SER)
unnamed: U29.9 (QH'), U33.14 (SER)
unnamed: U29.14 (SER), U36.9 (QH')
unnamed: U30.9 (QH'), U34.14 (SER)
unnamed: U30.14 (SER), U37.9 (QH')
unnamed: U31.9 (QH'), U35.14 (SER)
unnamed: U31.14 (SER), U38.9 (QH')
unnamed: U32.9 (QH'), U36.14 (SER)
unnamed: U33.9 (QH'), U37.14 (SER)
unnamed: U34.9 (QH'), U38.14 (SER)
unnamed: U35.9 (QH'), U39.14 (SER)
SHIFTREG_Clock: J25.2, U1.72 (PA11), U28.11 (SRCLK), U29.11 (SRCLK), U30.11 (SRCLK), U31.11 (SRCLK), U32.11 (SRCLK), U33.11 (SRCLK), U34.11 (SRCLK), U35.11 (SRCLK), U36.11 (SRCLK), U37.11 (SRCLK), U38.11 (SRCLK), U39.11 (SRCLK)
SHIFTREG_Data: J25.1, U1.73 (PA12), U28.14 (SER)
SHIFTREG_Latch: J25.3, U1.20 (PA0), U28.12 (RCLK), U29.12 (RCLK), U30.12 (RCLK), U31.12 (RCLK), U32.12 (RCLK), U33.12 (RCLK), U34.12 (RCLK), U35.12 (RCLK), U36.12 (RCLK), U37.12 (RCLK), U38.12 (RCLK), U39.12 (RCLK)
SWDCK: J1.6 (JCLK/SWCLK), U1.77 (PA14)
SWDIO: J1.4 (JTMS/SWDIO), U1.76 (PA13)
USART2_RX: J1.13 (VCP_RX), U1.25 (PA3)
USART2_TX: J1.14 (VCP_TX), U1.22 (PA2)
xPA7: J21.12, U1.29 (PA7)
xPB7: J21.1, U1.94 (PB7)
xPC14: J21.7, U1.8 (PC14)
xPC15: J21.10, U1.9 (PC15)
xPD3: J21.2, U1.85 (PD3)
xPE0: J21.4, U1.97 (PE0)
xPE1: J21.3, U1.98 (PE1)
xPE2: J21.6, U1.1 (PE2)
xPE5: J21.5, U1.4 (PE5)
xPE6: J21.8, U1.5 (PE6)
xPF9: J21.9, U1.10 (PF9)

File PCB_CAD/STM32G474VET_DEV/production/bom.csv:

Designator,Footprint,Quantity,Value,LCSC Part #
"C1, C2",0603,2,20p,C1648
"C10, C100, C101, C102, C103, C104, C105, C106, C107, C108, C109, C11, C110, C111, C112, C113, C114, C115, C116, C117, C118, C119, C12, C120, C121, C122, C123, C124, C125, C126, C127, C128, C129, C13, C130, C131, C132, C133, C134, C135, C136, C137, C138, C139, C14, C140, C141, C142, C143, C144, C145, C146, C147, C148, C149, C15, C150, C151, C152, C153, C154, C155, C156, C157, C158, C159, C16, C160, C161, C162, C163, C164, C165, C166, C167, C168, C169, C170, C171, C172, C173, C174, C175, C176, C177, C178, C179, C180, C181, C22, C29, C3, C35, C36, C37, C38, C5, C62, C63, C64, C65, C66, C67, C68, C69, C7, C70, C71, C72, C73, C74, C75, C76, C77, C78, C79, C8, C80, C81, C82, C83, C84, C85, C86, C87, C88, C89, C9, C90, C91, C92, C93, C94, C95, C96, C97, C98, C99",0603,138,100n,C1590
"C4, C6",0603,2,1u,C1592
"C41, C42, C47, C48, C49, C50, C60, C61",1206,8,10u,C1849
"D4, D5",TO-92,2,2N5062,
DZ1,D_SOD-123,1,MMSZ5227B,C707159
DZ2,D_SOD-123,1,MMSZ5233BT1G,C145506
FB1,Ferrite_0603_1608Metric,1,FerriteBead,C1002
J1,FTSH-107-01-L-DV-K-TR,1,STLINK,C5307809
J17,TE_2-1734839-2_1x22-1MP_P0.5mm_Horizontal,1,DISP0,C22435644
J18,TE_2-1734839-2_1x22-1MP_P0.5mm_Horizontal,1,DISP1,C22435644
J19,TE_2-1734839-2_1x22-1MP_P0.5mm_Horizontal,1,DISP2,C22435644
J2,PinHeader_2x12_P1.27mm_Vertical,1,FADER,
J20,TE_2-1734839-2_1x22-1MP_P0.5mm_Horizontal,1,DISP3,C22435644
J26,PinHeader_2x12_P1.27mm_Vertical,1,CV_SW_1,
J27,PinHeader_2x12_P1.27mm_Vertical,1,CV_SW_2,
J28,PinHeader_2x12_P1.27mm_Vertical,1,CV_SW_4,
J29,PinHeader_2x12_P1.27mm_Vertical,1,CV_SW_3,
J3,PinHeader_2x12_P1.27mm_Vertical,1,CRTL BRD,
"J4, J5",PinHeader_2x16_P2.54mm_Vertical,2,Conn_02x16_Odd_Even,
J7,PinHeader_1x06_P2.54mm_Vertical,1,SPI_MASTER,
J8,PinHeader_1x04_P2.54mm_Vertical,1,EXT_POW_IN,
Q1,SOT-23,1,2N7002,C85047
"R1, R18, R19, R20, R21",1206,5,390,C497314
"R15, R22",0603,2,1k,C21190
"R16, R23",0603,2,680,C25822
R17,0603,1,3.3k,C22978
R2,0603,1,10k,
R25,1206,1,68,C294793
"R26, R27",0603,2,47k,C25819
SW1,SW_Push_1P1T_NO_CK_KMR2,1,RESET,C72443
"TP10, TP11, TP19, TP9",TestPoint_Keystone_5019_Miniature,4,TestPoint_Probe,
U1,LQFP-100_14x14mm_P0.5mm,1,STM32G474VETx,C2970837
"U28, U29, U30, U31, U32, U33, U34, U35, U36, U37, U38, U39",TSSOP-16_4.4x5mm_P0.65mm,12,74HC595,C5948
X1,Crystal_SMD_HC49-SD,1,HSE_24,C117881

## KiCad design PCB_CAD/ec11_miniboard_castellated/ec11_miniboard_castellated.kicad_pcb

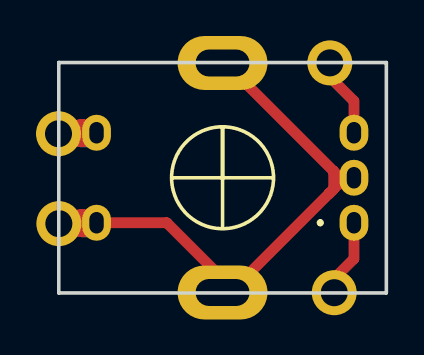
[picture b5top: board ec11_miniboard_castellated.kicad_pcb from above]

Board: 2 copper layers, 18.2 x 12.8 mm, 5 parts (0 on the bottom side), 4 nets.

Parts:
J1, J2, J3, J4: Conn_01x01; castellated_single
SW1: EC11_Rotary_Encoder; EC11J0924411

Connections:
GND: J4.1 (Pin_1_1), SW1.C (Pin_2), SW1.D (Pin_4), SW1.G (Pin_6)
unnamed: J1.1 (Pin_1_1), SW1.A (Pin_1)
unnamed: J2.1 (Pin_1_1), SW1.B (Pin_3)
unnamed: J3.1 (Pin_1_1), SW1.E (Pin_5)

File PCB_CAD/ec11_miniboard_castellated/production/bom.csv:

Designator,Footprint,Quantity,Value,LCSC Part #
"J1, J2, J3, J4",castellated_single,4,Conn_01x01,
SW1,EC11J0924411,1,EC11_Rotary_Encoder,
